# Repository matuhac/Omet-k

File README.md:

# Ometak

Cílem projektu je navrhnout jednoduchou řídící desku pro včelařský ometák.

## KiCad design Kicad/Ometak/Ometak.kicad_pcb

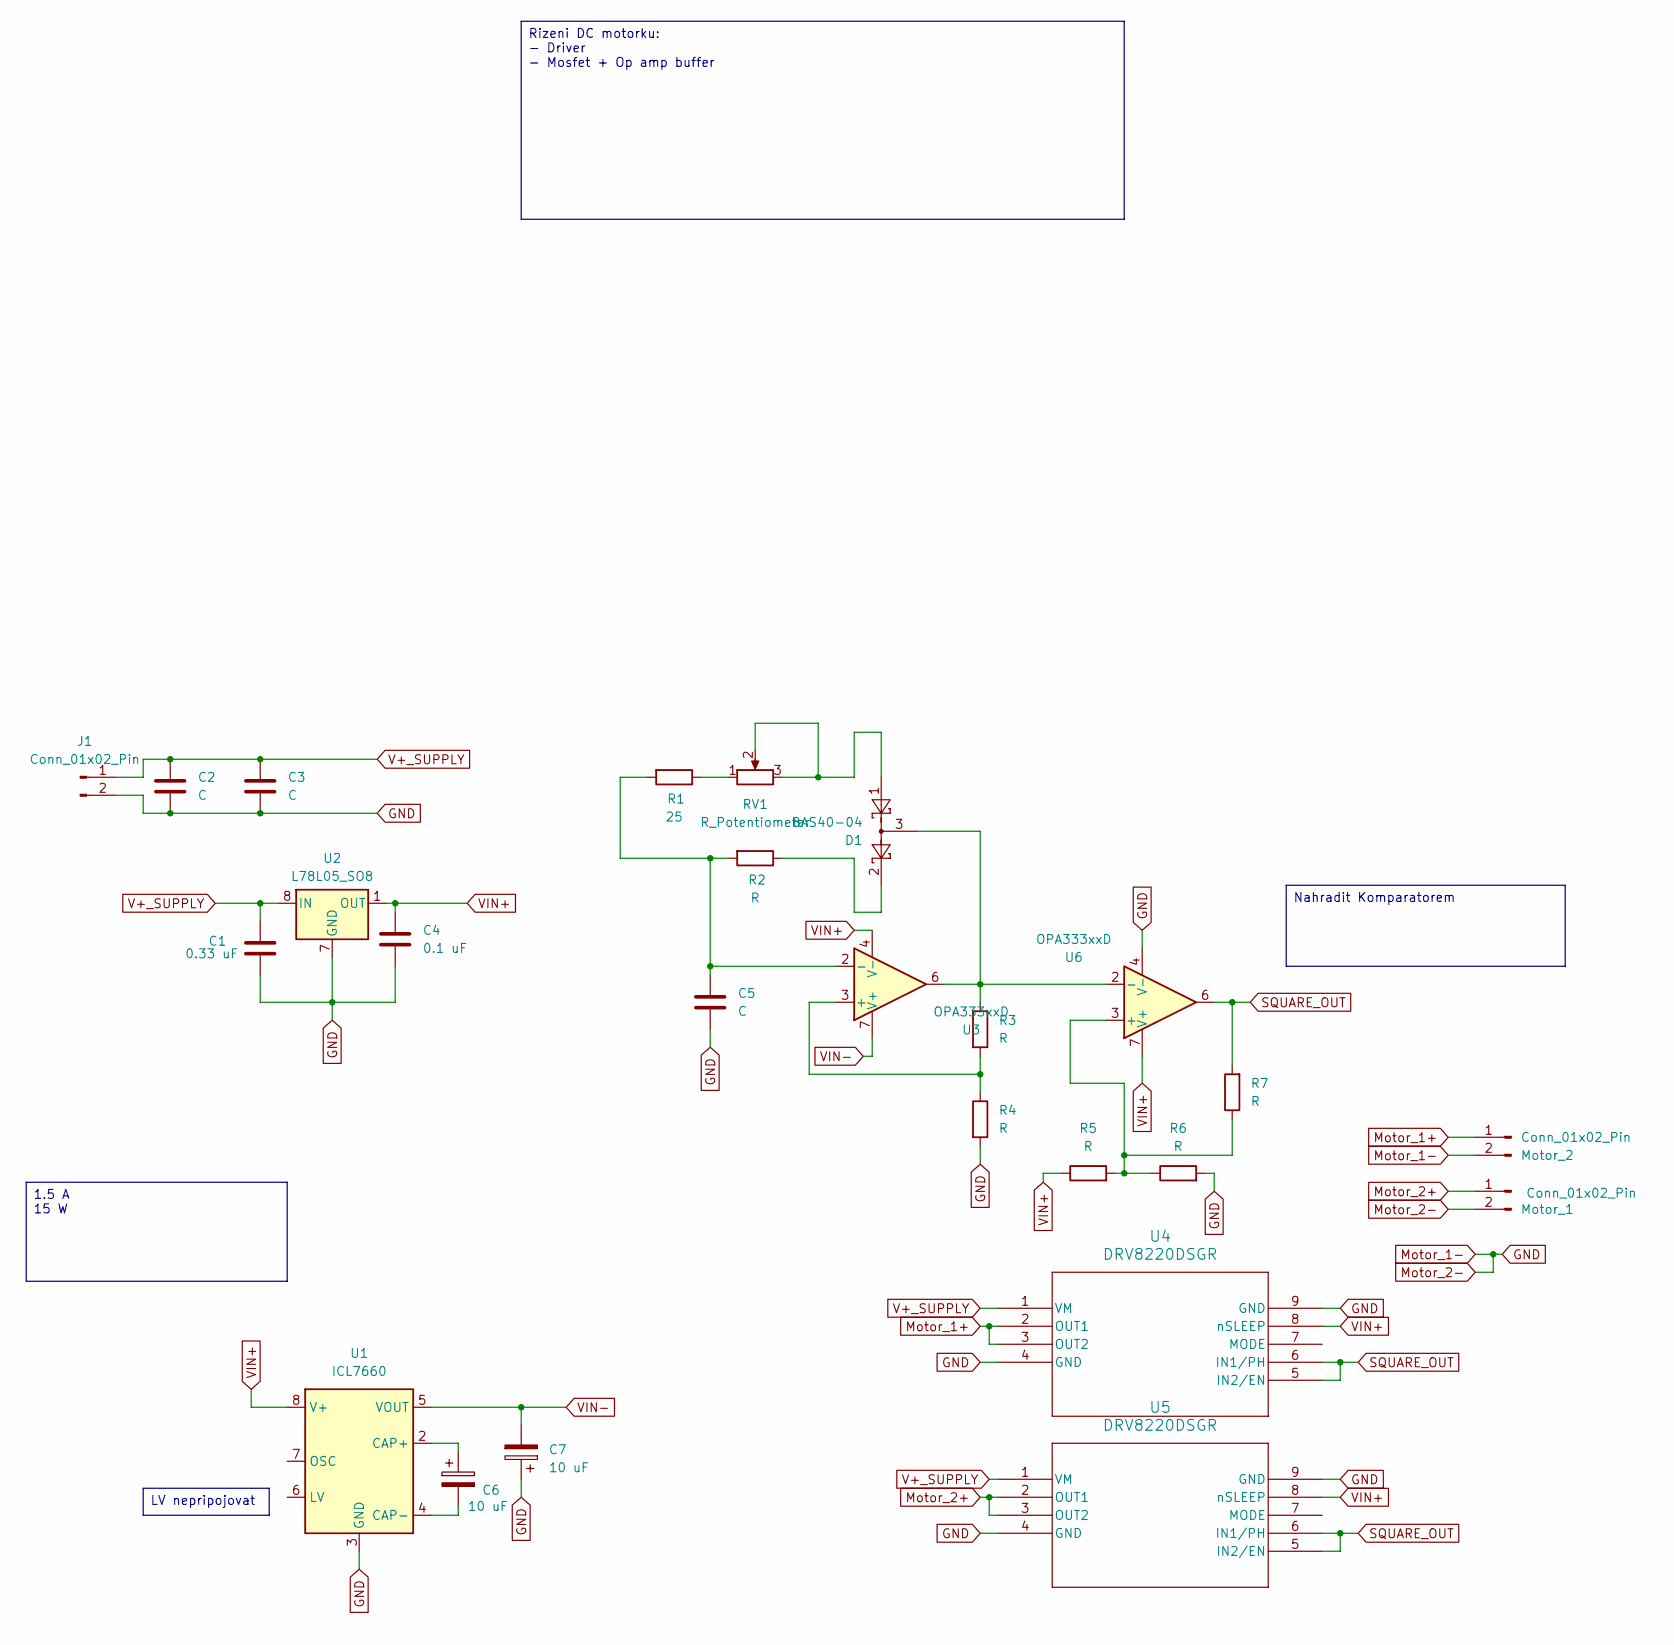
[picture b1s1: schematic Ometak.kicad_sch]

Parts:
C1: 0.33 uF; C_1206_3216Metric
C2, C3: C; CP_Radial_D10.0mm_P5.00mm
C4: 0.1 uF; C_1206_3216Metric
C5: C; C_1206_3216Metric
C6, C7: 10 uF; C_1206_3216Metric
D1: BAS40-04; SOT-23
J1: Conn_01x02_Pin; TerminalBlock_MaiXu_MX126-5.0-02P_1x02_P5.00mm
Motor_1, Motor_2: Conn_01x02_Pin; TerminalBlock_MaiXu_MX126-5.0-02P_1x02_P5.00mm
R1: 25; R_1206_3216Metric
R2, R3, R4, R5, R6, R7: R; R_1206_3216Metric
RV1: R_Potentiometer; Potentiometer_Piher_PC-16_Single_Horizontal
U1: ICL7660; SOIC-8_3.9x4.9mm_P1.27mm
U2: L78L05_SO8; SOIC-8_3.9x4.9mm_P1.27mm
U3, U6: OPA333xxD; SOIC-8_3.9x4.9mm_P1.27mm
U4, U5: DRV8220DSGR; WSON8_DSG_TEX

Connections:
GND: C1.2, C2.2, C3.2, C4.2, C5.2, C7.1, J1.2, Motor_1.2, Motor_2.2, R4.2, R6.2, U1.3 (GND), U2.2 (GND), U2.3 (GND), U2.6 (GND), U2.7 (GND), U4.4 (GND), U4.9 (GND), U5.4 (GND), U5.9 (GND), U6.4 (V-)
Motor_1+: Motor_2.1, U4.2 (OUT1), U4.3 (OUT2)
Motor_2+: Motor_1.1, U5.2 (OUT1), U5.3 (OUT2)
unnamed: D1.1, RV1.2, RV1.3
unnamed: D1.2, R2.1
unnamed: R1.1, RV1.1
unnamed: C6.1, U1.2 (CAP+)
unnamed: C6.2, U1.4 (CAP-)
unnamed: R3.2, R4.1, U3.3 (+)
unnamed: C5.1, R1.2, R2.2, U3.2 (-)
unnamed: R5.2, R6.1, R7.1, U6.3 (+)
unnamed: D1.3, R3.1, U3.6, U6.2 (-)
SQUARE_OUT: R7.2, U4.5 (IN2/EN), U4.6 (IN1/PH), U5.5 (IN2/EN), U5.6 (IN1/PH), U6.6
V+_SUPPLY: C1.1, C2.1, C3.1, J1.1, U2.8 (IN), U4.1 (VM), U5.1 (VM)
VIN+: C4.1, R5.1, U1.8 (V+), U2.1 (OUT), U3.4 (V-), U4.8 (nSLEEP), U5.8 (nSLEEP), U6.7 (V+)
VIN-: C7.2, U1.5 (VOUT), U3.7 (V+)

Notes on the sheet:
LV nepripojovat
1.5 A 15 W
Nahradit Komparatorem
Rizeni DC motorku: - Driver - Mosfet + Op amp buffer

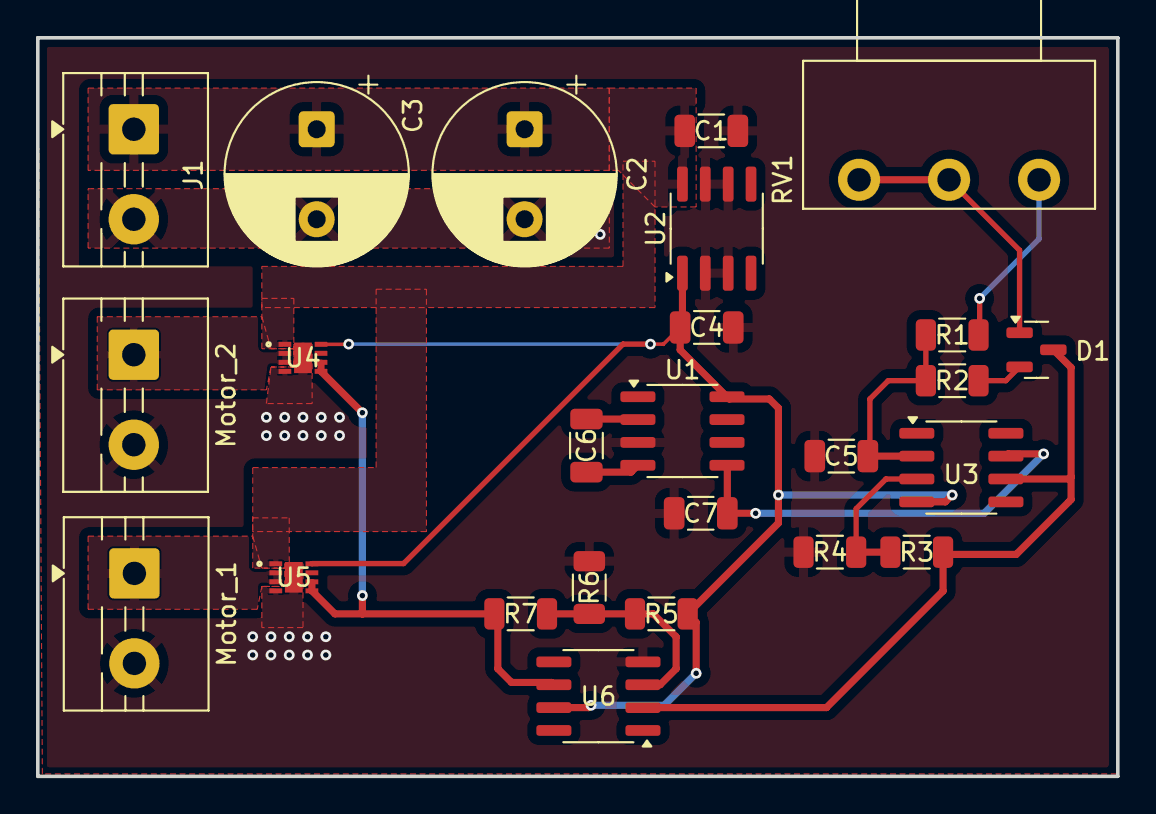
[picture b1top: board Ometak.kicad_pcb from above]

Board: 2 copper layers, 60.0 x 41.0 mm, 25 parts (0 on the bottom side), 16 nets.

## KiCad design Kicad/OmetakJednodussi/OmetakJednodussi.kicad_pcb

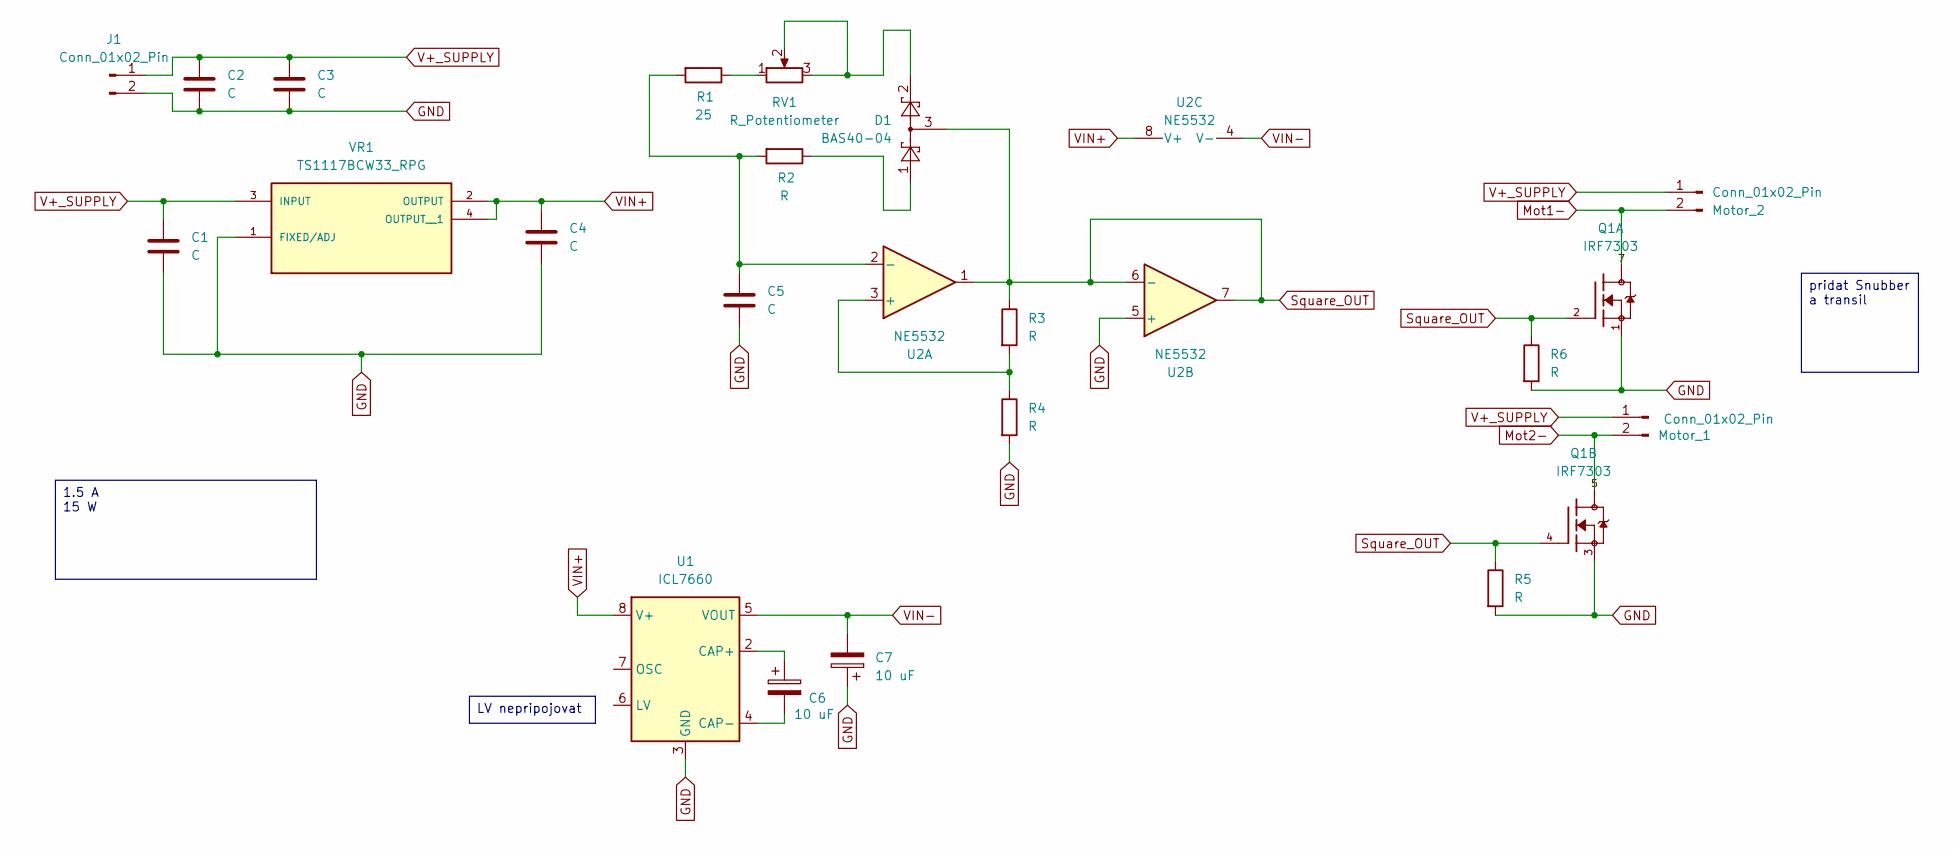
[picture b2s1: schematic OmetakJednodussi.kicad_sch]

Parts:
C1, C4, C5: C; C_1206_3216Metric
C2, C3: C; CP_Radial_D10.0mm_P5.00mm
C6, C7: 10 uF; C_1206_3216Metric
D1: BAS40-04; SOT-23
J1: Conn_01x02_Pin; TerminalBlock_MaiXu_MX126-5.0-02P_1x02_P5.00mm
Motor_1, Motor_2: Conn_01x02_Pin; TerminalBlock_MaiXu_MX126-5.0-02P_1x02_P5.00mm
Q1: IRF7303; SOIC-8
R1: 25; R_1206_3216Metric
R2, R3, R4, R5, R6: R; R_1206_3216Metric
RV1: R_Potentiometer; Potentiometer_Piher_PC-16_Single_Horizontal
U1: ICL7660; SOIC-8_3.9x4.9mm_P1.27mm
U2: NE5532; SOIC-8_5.3x6.2mm_P1.27mm
VR1: TS1117BCW33_RPG; VREG_TS1117BCW33_RPG; PARTREV H1607

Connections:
GND: C1.2, C2.2, C3.2, C4.2, C5.2, C7.1, J1.2, Q1.1, Q1.3, R4.2, R5.2, R6.2, U1.3 (GND), U2.5 (+), VR1.1 (FIXED/ADJ)
Mot1-: Motor_2.2, Q1.7, Q1.8
Mot2-: Motor_1.2, Q1.5, Q1.6
unnamed: D1.1, R2.1
unnamed: D1.2, RV1.2, RV1.3
unnamed: R1.1, RV1.1
unnamed: C6.1, U1.2 (CAP+)
unnamed: C6.2, U1.4 (CAP-)
unnamed: R3.2, R4.1, U2.3 (+)
unnamed: C5.1, R1.2, R2.2, U2.2 (-)
Square_OUT: D1.3, Q1.2, Q1.4, R3.1, R5.1, R6.1, U2.1, U2.6 (-), U2.7
V+_SUPPLY: C1.1, C2.1, C3.1, J1.1, Motor_1.1, Motor_2.1, VR1.3 (INPUT)
VIN+: C4.1, U1.8 (V+), U2.8 (V+), VR1.2 (OUTPUT), VR1.4 (OUTPUT__1)
VIN-: C7.2, U1.5 (VOUT), U2.4 (V-)

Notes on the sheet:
LV nepripojovat
pridat Snubber a transil
1.5 A 15 W

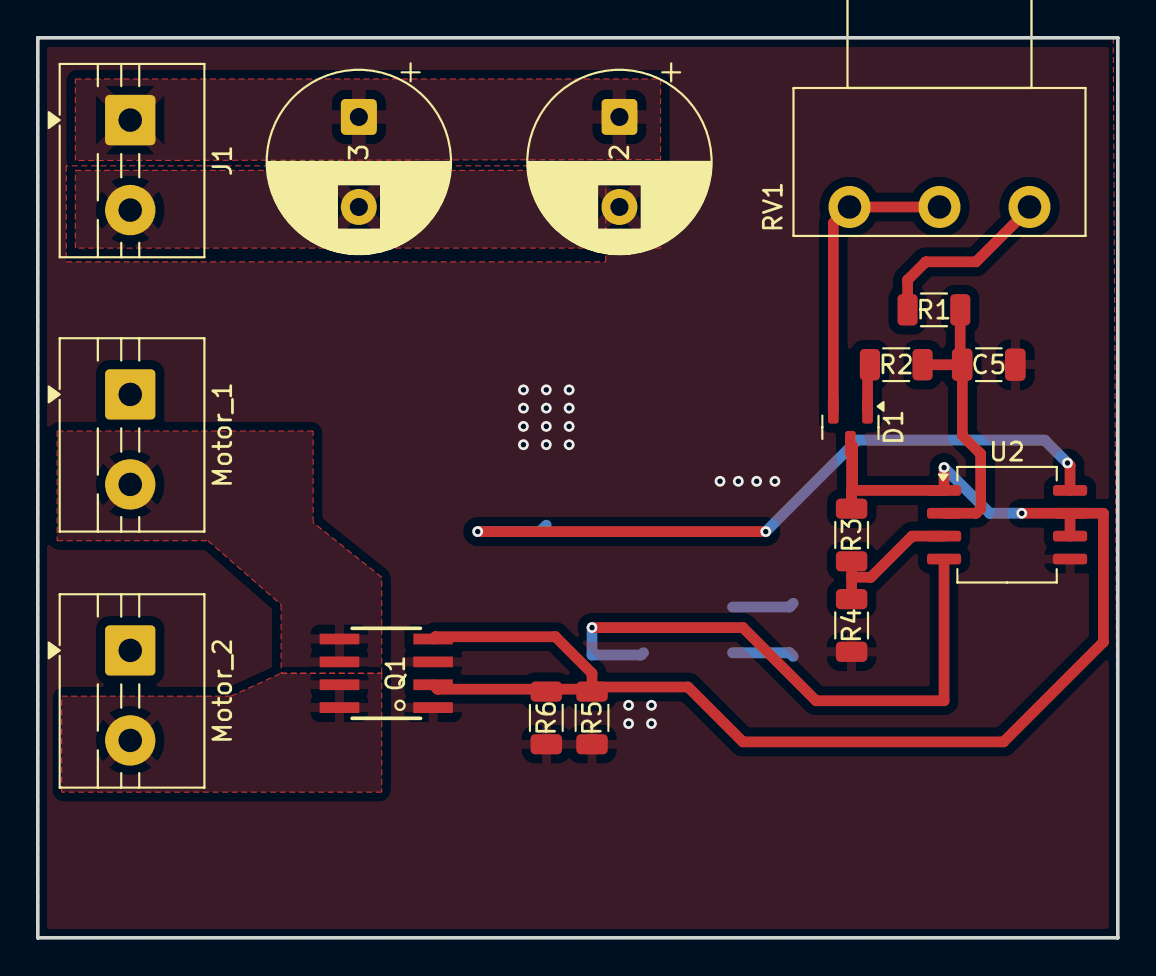
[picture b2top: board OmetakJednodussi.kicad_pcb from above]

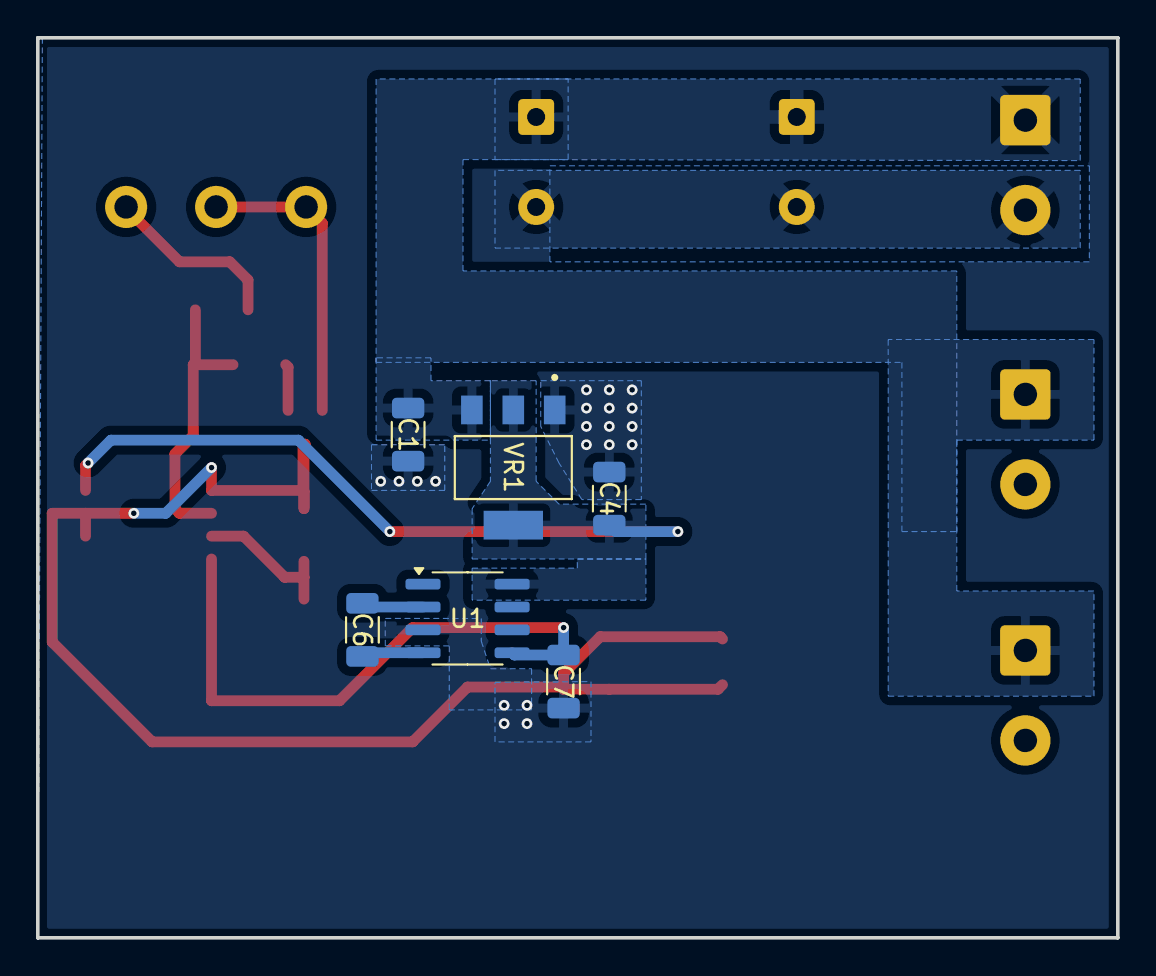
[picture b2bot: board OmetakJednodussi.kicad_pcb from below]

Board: 2 copper layers, 60.0 x 50.0 mm, 22 parts (6 on the bottom side), 14 nets.

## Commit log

2026-04-13 Pridani souboru - Kicad a CubeIDE
    Pridani uz vytvorenych souboru.
2026-05-02 Update jednodussi verze
2026-05-21 Jednoduchy design navrh
2026-05-22 Pokrocilejsi verze ometaku - navrh
